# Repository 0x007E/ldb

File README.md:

# `LDB` - LED Development Board

The `LDB` is a board with 10 LEDs and a 7-Segment display with a [MC14543](#additional-information) or any other `BCD/7-Segment` converter that meets the pin requirements. The board itself can be driven from `3` to `15V`. The board offers the possibility to convert a bcd number to a 7-segment display or control a set of leds by driving buttons, switches or any other logic board elements.

| Experience  | Level                                                                               |
|:------------|:-----------------------------------------------------------------------------------:|
| Soldering   |  |

# Downloads

| Type      | File                                                                                                                                                 | Description     |
|:---------:|:----------------------------------------------------------------------------------------------------------------------------------------------------:|:----------------|
| Schematic | [pdf](https://github.com/0x007E/ldb/releases/latest/download/schematic.pdf) / [cadlab](https://cadlab.io/project/30142/main/files)                   | Schematic files |
| Board     | [pdf](https://github.com/0x007E/ldb/releases/latest/download/pcb.pdf) / [cadlab](https://cadlab.io/project/30142/main/files)                         | Board file      |
| Drill     | [pdf](https://github.com/0x007E/ldb/releases/latest/download/drill.pdf)                                                                              | Drill file      |
| PCB       | [zip](https://github.com/0x007E/ldb/releases/latest/download/kicad.zip) / [tar](https://github.com/0x007E/ldb/releases/latest/download/kicad.tar.gz) | KiCAD/Gerber/BoM/Drill files |
| Mechanical | [zip](https://github.com/0x007E/ldb/releases/latest/download/freecad.zip) / [tar](https://github.com/0x007E/ldb/releases/latest/download/freecad.tar.gz) | FreeCAD/Housing and exported step/stl files |

# Hardware

The pcb is created with `KiCAD`. All files are built with `github actions` so that they are ready for a production environment.

## PCB

The circuit board is populated on both sides (Top, Bottom). The best way for soldering the `SMD` components is within a vapor phase soldering system and for the `THT` components with a standard soldering system.

### Top Layer

### Bottom Layer

# Additional Information

| Type       | Link                                                       | Description                                                   |
|:----------:|:----------------------------------------------------------:|:--------------------------------------------------------------|
| MC14543    | [pdf](https://www.onsemi.com/pdf/datasheet/mc14543b-d.pdf) | BCD-to-Seven Segment Latch/Decoder/Driver for Liquid Crystals |

---

R. GAECHTER

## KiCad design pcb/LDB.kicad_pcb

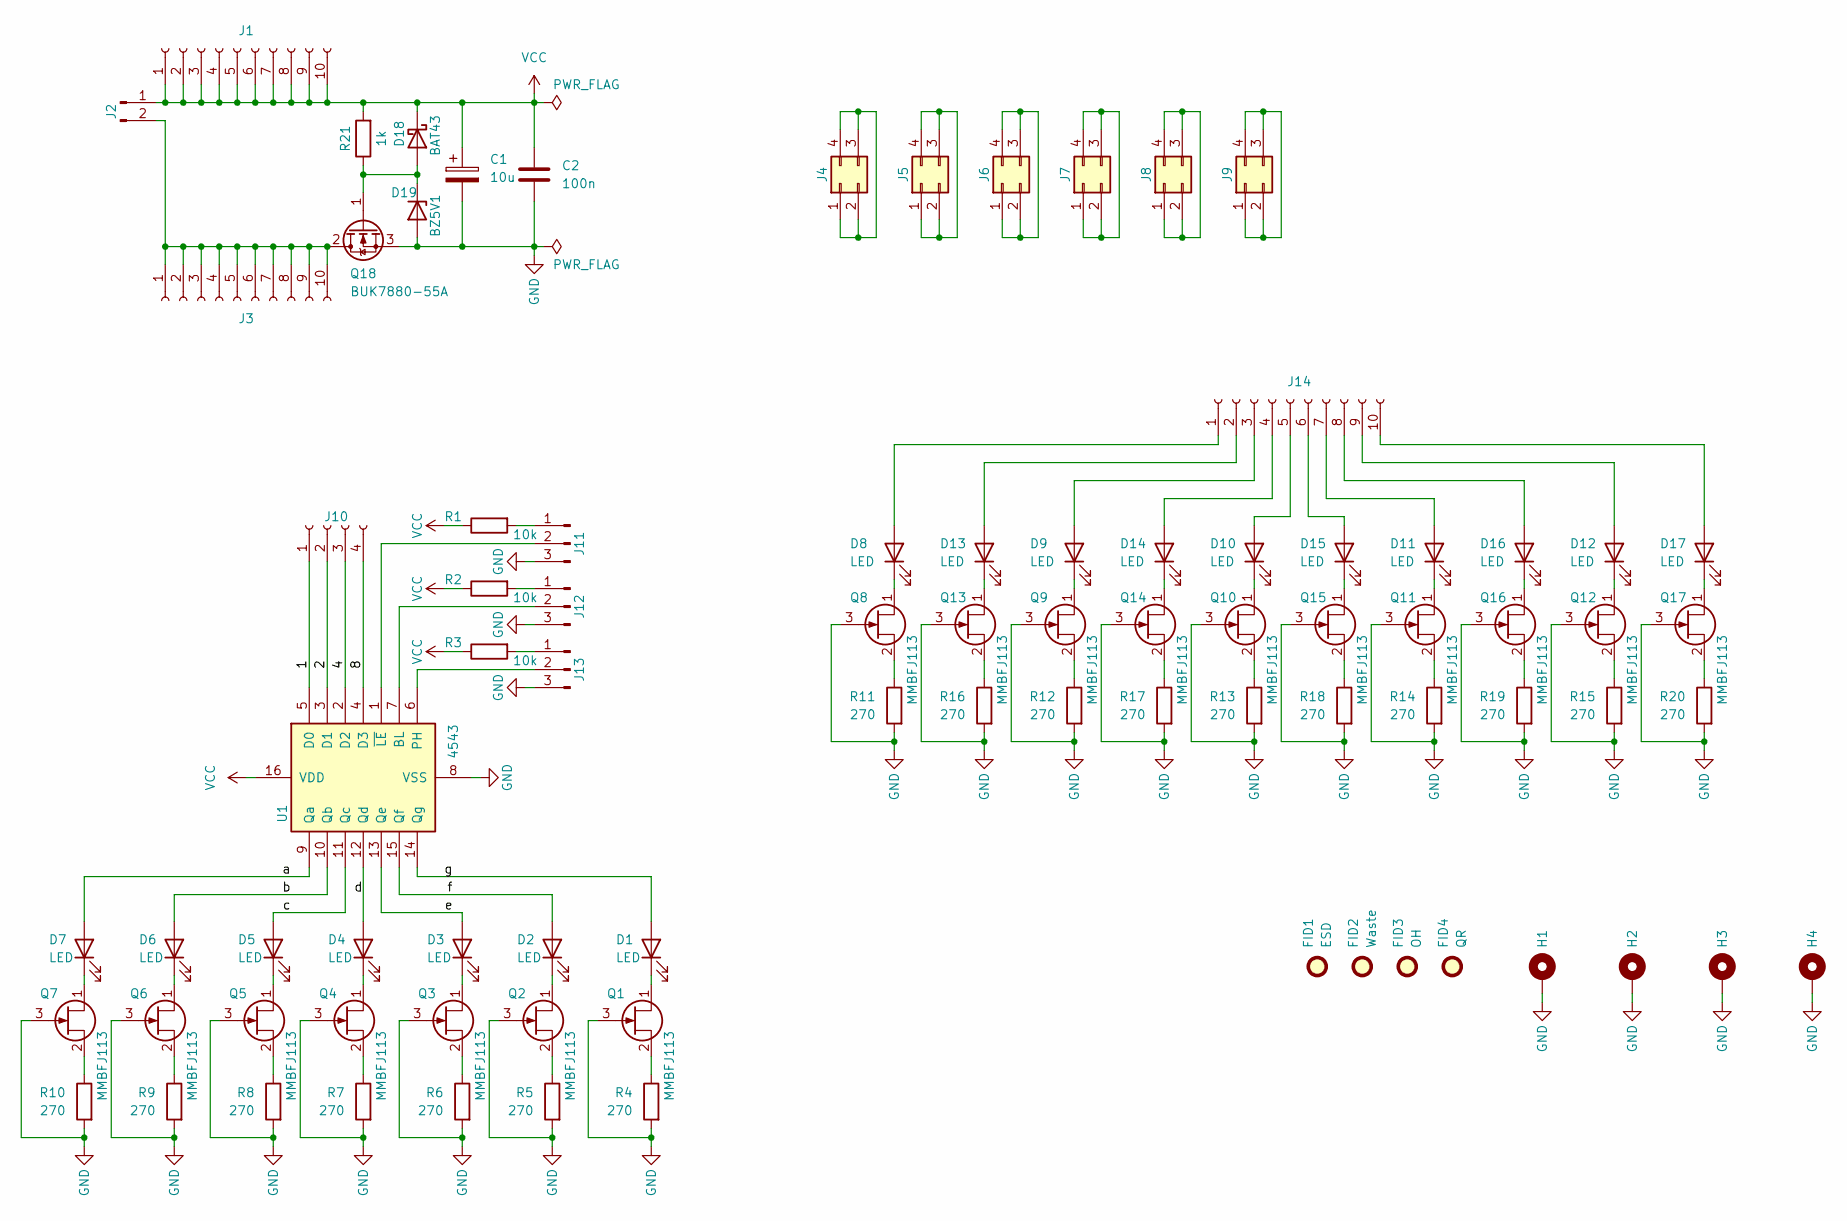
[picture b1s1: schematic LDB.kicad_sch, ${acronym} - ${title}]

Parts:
C1: 10u; CP_Radial_D6.3mm_P2.50mm
C2: 100n; C_1206_3216Metric
D1, D2, D3, D4, D5, D6, D7: LED; LED_Rectangular_W5.0mm_H2.0mm
D8, D9, D10, D11, D12, D13, D14, D15, D16, D17: LED; LED_D5.0mm
D18: BAT43; D_MiniMELF
D19: BZ5V1; D_MiniMELF
FID1: ESD; ESD-Logo_6.6x6mm_SilkScreen
FID2: Waste; WEEE-Logo_4.2x6mm_SilkScreen
FID3: OH; OSHW-Logo_5.7x6mm_SilkScreen
FID4: QR; QR_0x007e
H1, H2, H3, H4: MountingHole_Pad; MountingHole_3.2mm_M3_Pad
J1, J3, J14: Conn_01x10_Socket; PinSocket_1x10_P2.54mm_Vertical
J2: Conn_01x02_Pin; PinHeader_1x02_P2.54mm_Vertical
J4, J5, J6, J7, J8, J9: Conn_02x02_Counter_Clockwise; PinSocket_2x02_P2.54mm_Vertical
J10: Conn_01x04_Socket; PinSocket_1x04_P2.54mm_Vertical
J11, J12, J13: Conn_01x03_Pin; PinHeader_1x03_P2.54mm_Vertical
Q1, Q2, Q3, Q4, Q5, Q6, Q7, Q8, Q9, Q10, Q11, Q12, Q13, Q14, Q15, Q16, Q17: MMBFJ113; SOT-23
Q18: BUK7880-55A; SOT-223-3_TabPin2
R1, R2, R3: 10k; R_1206_3216Metric
R4, R5, R6, R7, R8, R9, R10, R11, R12, R13, R14, R15, R16, R17, R18, R19, R20: 270; R_1206_3216Metric
R21: 1k; R_1206_3216Metric
U1: 4543; SOIC-16_3.9x9.9mm_P1.27mm

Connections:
/1: J10.1, U1.5 (D0)
/2: J10.2, U1.3 (D1)
/4: J10.3, U1.2 (D2)
/8: J10.4, U1.4 (D3)
/a: D7.2 (A), U1.9 (Qa)
/b: D6.2 (A), U1.10 (Qb)
/c: D5.2 (A), U1.11 (Qc)
/d: D4.2 (A), U1.12 (Qd)
/e: D3.2 (A), U1.13 (Qe)
/f: D2.2 (A), U1.15 (Qf)
/g: D1.2 (A), U1.14 (Qg)
GND: C1.2, C2.2, D19.2 (A), H1.1, H2.1, H3.1, H4.1, J11.3, J12.3, J13.3, Q1.3 (G), Q2.3 (G), Q3.3 (G), Q4.3 (G), Q5.3 (G), Q6.3 (G), Q7.3 (G), Q8.3 (G), Q9.3 (G), Q10.3 (G), Q11.3 (G), Q12.3 (G), Q13.3 (G), Q14.3 (G), Q15.3 (G), Q16.3 (G), Q17.3 (G), Q18.3 (S), R4.2, R5.2, R6.2, R7.2, R8.2, R9.2, R10.2, R11.2, R12.2, R13.2, R14.2, R15.2, R16.2, R17.2, R18.2, R19.2, R20.2, U1.8 (VSS)
unnamed: D1.1 (K), Q1.1 (D)
unnamed: D2.1 (K), Q2.1 (D)
unnamed: D3.1 (K), Q3.1 (D)
unnamed: D4.1 (K), Q4.1 (D)
unnamed: D5.1 (K), Q5.1 (D)
unnamed: D6.1 (K), Q6.1 (D)
unnamed: D7.1 (K), Q7.1 (D)
unnamed: D8.2 (A), J14.1
unnamed: D8.1 (K), Q8.1 (D)
unnamed: D9.2 (A), J14.3
unnamed: D9.1 (K), Q9.1 (D)
unnamed: D10.2 (A), J14.5
unnamed: D10.1 (K), Q10.1 (D)
unnamed: D11.2 (A), J14.7
unnamed: D11.1 (K), Q11.1 (D)
unnamed: D12.2 (A), J14.9
unnamed: D12.1 (K), Q12.1 (D)
unnamed: D13.2 (A), J14.2
unnamed: D13.1 (K), Q13.1 (D)
unnamed: D14.2 (A), J14.4
unnamed: D14.1 (K), Q14.1 (D)
unnamed: D15.2 (A), J14.6
unnamed: D15.1 (K), Q15.1 (D)
unnamed: D16.2 (A), J14.8
unnamed: D16.1 (K), Q16.1 (D)
unnamed: D17.2 (A), J14.10
unnamed: D17.1 (K), Q17.1 (D)
unnamed: D18.2 (A), D19.1 (K), Q18.1 (G), R21.1
unnamed: J2.2, J3.1, J3.2, J3.3, J3.4, J3.5, J3.6, J3.7, J3.8, J3.9, J3.10, Q18.2 (D)
unnamed: J4.1, J4.2, J4.3, J4.4
unnamed: J5.1, J5.2, J5.3, J5.4
unnamed: J6.1, J6.2, J6.3, J6.4
unnamed: J7.1, J7.2, J7.3, J7.4
unnamed: J8.1, J8.2, J8.3, J8.4
unnamed: J9.1, J9.2, J9.3, J9.4
unnamed: J11.1, R1.2
unnamed: J11.2, U1.1 (~LE)
unnamed: J12.1, R2.2
unnamed: J12.2, U1.7 (BL)
unnamed: J13.1, R3.2
unnamed: J13.2, U1.6 (PH)
unnamed: Q1.2 (S), R4.1
unnamed: Q2.2 (S), R5.1
unnamed: Q3.2 (S), R6.1
unnamed: Q4.2 (S), R7.1
unnamed: Q5.2 (S), R8.1
unnamed: Q6.2 (S), R9.1
unnamed: Q7.2 (S), R10.1
unnamed: Q8.2 (S), R11.1
unnamed: Q9.2 (S), R12.1
unnamed: Q10.2 (S), R13.1
unnamed: Q11.2 (S), R14.1
unnamed: Q12.2 (S), R15.1
unnamed: Q13.2 (S), R16.1
unnamed: Q14.2 (S), R17.1
unnamed: Q15.2 (S), R18.1
unnamed: Q16.2 (S), R19.1
unnamed: Q17.2 (S), R20.1
VCC: C1.1, C2.1, D18.1 (K), J1.1, J1.2, J1.3, J1.4, J1.5, J1.6, J1.7, J1.8, J1.9, J1.10, J2.1, R1.1, R2.1, R3.1, R21.2, U1.16 (VDD)

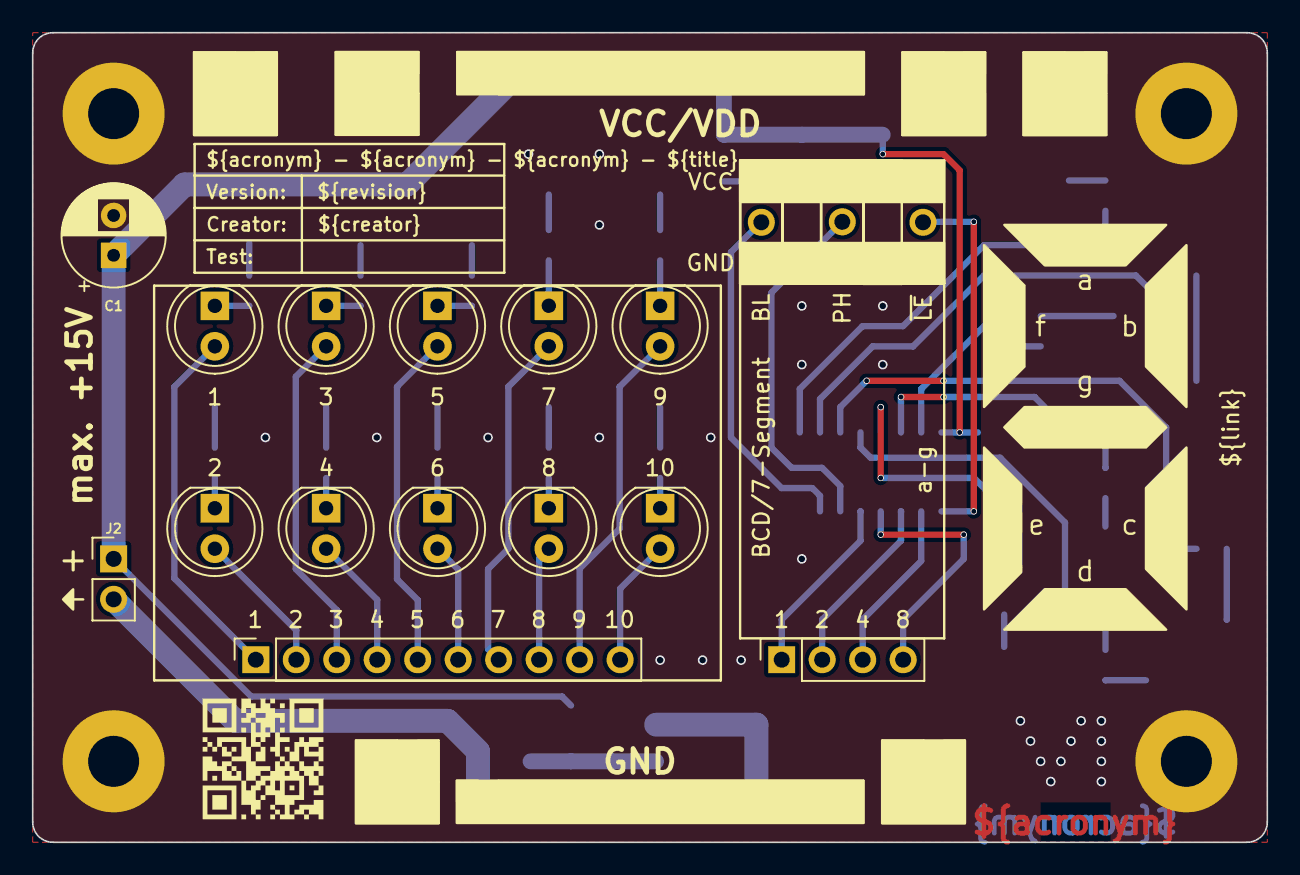
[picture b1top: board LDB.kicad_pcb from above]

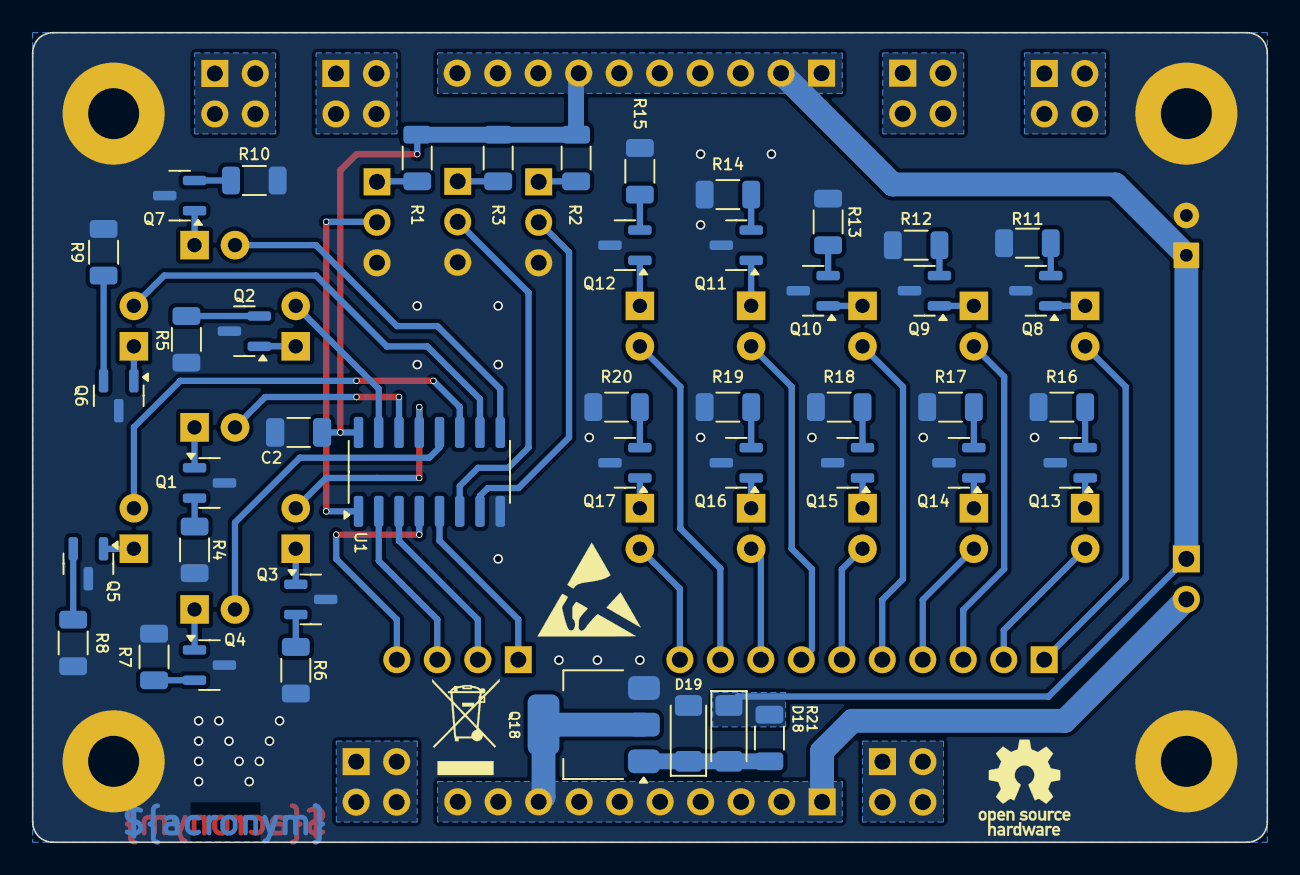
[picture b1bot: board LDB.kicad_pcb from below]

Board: 2 copper layers, 77.5 x 50.8 mm, 83 parts (46 on the bottom side), 71 nets.

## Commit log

2026-03-09 Add pcb layout
2026-03-09 Add LT-Spice files
2026-03-09 Add README.md
2026-03-09 Add build pipeline
2026-03-09 Add release pipeline
2026-03-09 Fix fabrication layer positions
2026-03-24 Adapt edge cuts and dimensioning
2026-03-24 Add FreeCAD modification and export
2026-03-24 Add mechanical download link
2026-04-15 Swap led positions
2026-04-15 Remove unnecessary filter
2026-05-09 Add reverse polarity protection
2026-05-11 Optimize fabrication layer
2026-05-12 Adapt description

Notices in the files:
README.md:
License CC By-NC-SA
parts and their libraries:
license: CC BY-NC-SA 4.0
